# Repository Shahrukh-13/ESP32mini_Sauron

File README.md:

# ESP32mini_Sauron
ESP32 LCD display for CSTM80 showing Sauton gif and disaplying date and time

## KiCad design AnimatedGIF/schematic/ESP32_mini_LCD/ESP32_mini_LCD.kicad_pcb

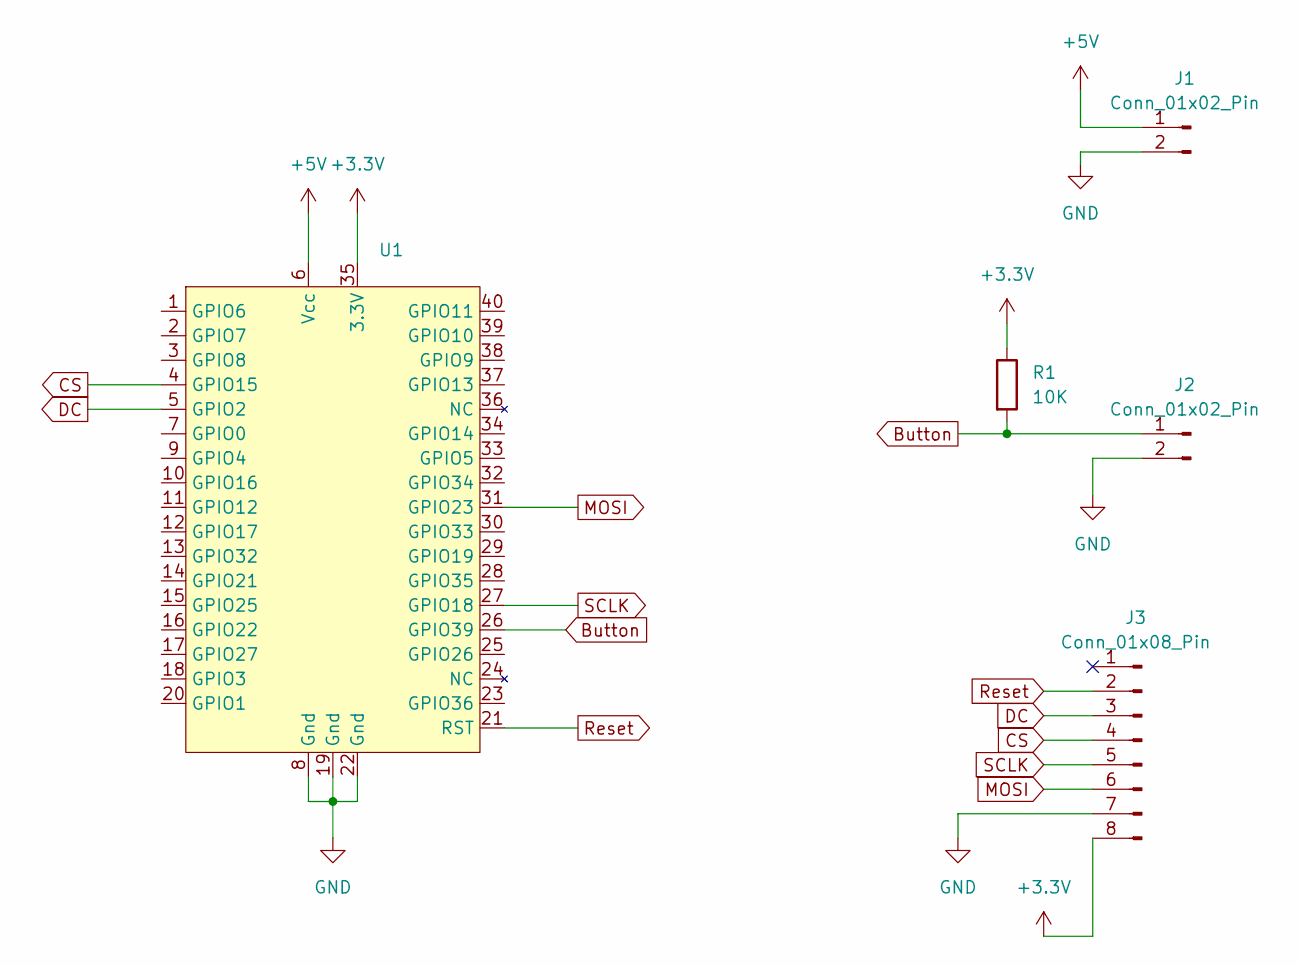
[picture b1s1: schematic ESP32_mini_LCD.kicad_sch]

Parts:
J1, J2: Conn_01x02_Pin; PinHeader_1x02_P2.54mm_Vertical
J3: Conn_01x08_Pin; PinHeader_1x08_P2.54mm_Vertical
R1: 10K; R_Axial_DIN0207_L6.3mm_D2.5mm_P10.16mm_Horizontal
U1: ESP32_mini

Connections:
+3.3V: J3.8, R1.1, U1.35 (3.3V)
+5V: J1.1, U1.6 (Vcc)
Button: J2.1, R1.2, U1.26 (GPIO39)
CS: J3.4, U1.4 (GPIO15)
DC: J3.3, U1.5 (GPIO2)
GND: J1.2, J2.2, J3.7, U1.8 (Gnd), U1.19 (Gnd), U1.22 (Gnd)
MOSI: J3.6, U1.31 (GPIO23)
Reset: J3.2, U1.21 (RST)
SCLK: J3.5, U1.27 (GPIO18)

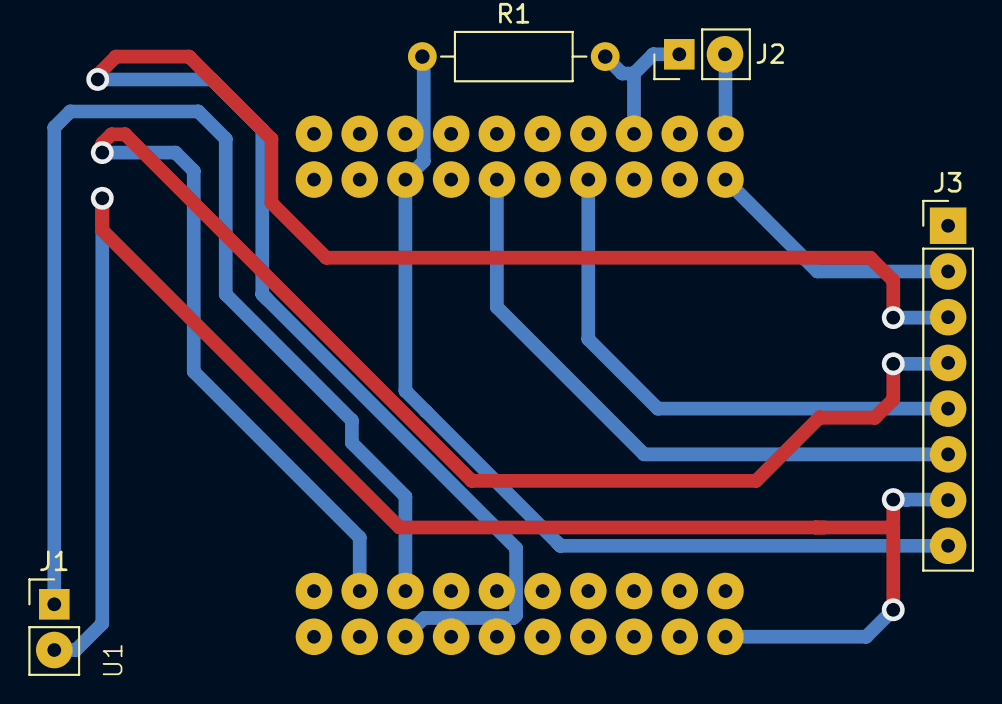
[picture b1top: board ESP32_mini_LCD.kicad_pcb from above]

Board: 2 copper layers, 5 parts (0 on the bottom side), 9 nets.
